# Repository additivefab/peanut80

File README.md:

# ZL80 R5.2｜80 mm 连续工业底片扫描仪

**当前设计基线更新于 2026-11-17，阶段为工程评审。** 从 [R5.2 融合设计基线](docs/ZL80_R52_融合评估与设计基线.md) 第 8 节进入，或打开 [离线目录](index.html)。

- [G4 板卡与装配](ZL80_R52_G4_20261116/START_HERE.html) 提供 B06/B07/B08 布线候选。B01 按 R5.2 双增益重版，B02–B05 待闭合。
- [G5 FPGA 与原始采集（Hello-FPGA 核心板修订）](ZL80_R52_G5_HF_20261117/START_HERE.html) 提供归一化采集核、第三路出口随动编码器和 ZL80RAW1 离线调试格式。Icarus 仿真通过；Vivado、B02 同 epoch 适配、时戳标定和 DMA 仍有待完成。
- [ADF50 V0.6](ZL80_ADF50_V06/README.md) 是现行馈片方案，单向走片、两处 R80 弯道，含已批准的 ECR-G3-01（出口随动编码器）、B05 第三路输入和线束。旧版 V01–V05 已于 2026-11-17 删除。

加工、投板和烧录状态为 BLOCKED。以下为 R5-PDR1 的原始交付说明，收光、板卡与馈片等变更以当前设计基线为准。

## R5-PDR1 原始交付

**交付日期：2026-11-14。阶段：光机电集成初步工程设计，不是加工/PCB投板放行。**

解压后打开`index.html`，无需联网浏览全部105张图纸。建议先看设计说明、D04板卡空间、D08积分筒剖面、D10 PMT接口、D13传感器、D17线束和E01–E08各板布局。

## 固定架构

80 mm有效幅宽；100 mm横扫预留；实体顶部狭缝104×1.2 mm。激光→准直/ND/参考取光→反射式旋转多面棱镜→f-theta→连续运动胶片→横置积分筒→径向侧窗→PMMA导光件→单PMT→模拟前端→DC耦合ADC→FPGA。圆筒轴X，片进给Y，Z向上，两端封闭。

首版模拟前端按新PPT采用线性TIA。原机LOG作为互斥的替换卡路线保留，不能把两者并接PMT。未设计普通相机、整线照明加单PMT或振镜替代路线。

## 本版关键改进

- 不只画板框：8块定制PCB草稿＋SP2托板定义了坐标、孔位、层数目标、上下器件高度、维护方向；84个关键器件或功能空间区域参与布置。
- PMT候选为H10720-20针脚式模块；8×10 mm入口导光件在输出端收至5.2 mm方形，针对φ8 mm有效光阴极重新起算。几何可容纳不代表导光效率已验证。
- PMT插座和短输入前端靠近布置；模拟舱、采集舱、驱动和开关电源分区；SP2接口按V1.3B并明确1.8/3.3/5V边界。
- 四辊连续走片，牵引与计量独立；SOS/EOS、参考PD、入出片、温度、开盖/失扫、可选馈片异常均在表格/图中定义位置及接口。
- 纳入插拔、线束、维护空间；关键器件突出空间与刚性核心复核；不把裸板能放入当成已完成整机装联。

## 文件目录

| 目录 | 内容 |
|---|---|
| docs | 25页设计说明PDF/DOCX及Markdown |
| drawings | 105页完整图册；32页系统+PCB；73页零件名义几何；逐张SVG/PNG |
| cad | 81个STEP、12个DXF、可编辑CadQuery脚本、装配坐标及空间限界 |
| electronics | 8个未布线KiCad PCB草稿、16张针脚/网名审查图、关键布局、接口/线束 |
| engineering | 13工作表Excel、预算JSON、机械/电子BOM、选型证据、14项冻结门槛 |
| firmware / software | 时序/编码器参考RTL与XDC、Python参考数据处理；不是可直接运行整机软件 |
| references | 原始资料、PPT逐页文本、照片、厂家来源登记 |
| tests | 实际执行的几何、空间、公式、文件版面和35项Python测试记录 |
| tools | 辅助生成/检查源代码与依赖说明 |

## 本次已执行检查

73个名义CAD形体有效，核心刚性件未发现体积重叠；关键器件空间盒与核心件复核无未解决碰撞（PMT插针/插座等预期接合单独标记）。35项计算和参考数据链测试通过。PDF最终渲染和Excel公式已检查。

这些检查**不代表**真实光学、PMT线性、高OD信噪比、胶片无划伤、EMC/安全或寿命已经合格。没有运行KiCad原生ERC/DRC，也没有完成RTL综合与时序验证。

## 明确未关闭的设计事项

关键光学器件需联合RFQ并锁定真实处方、工作距离和全视场光斑；SP2的110×60×25 mm仅保守安装限界，孔距/接口位置需实测；编码器量化步距不代表真实走片精度。B03/B04/B05等FUNCTION_ONLY区域需完成器件级电路、外围、焊盘、保护和完整PCB布线；全紧固、公差链、线束弯曲、装配工艺仍需深化。**本包不提供Gerber，不应按此直接下单生产。**

本版主机安装包络320×300×300 mm，不含外置卷架/馈片器。基座与铝外罩名义质量已约4.33 kg，整机试制预算6–8 kg待称重；**早期≤3.5 kg便携目标尚未实现**。优先验证核心链路后再进行减重和小型化，而非用缩小的占位盒宣称目标已达成。

## 数据/版本

文件校验见`manifest_sha256.json`。`release_status.json`为机器可读交付状态。所有性能数值注明来源或“设计假设/目标”，样机数据尚未提供。Raw Master和Calibrated Master与显示/AI派生图分开保存。

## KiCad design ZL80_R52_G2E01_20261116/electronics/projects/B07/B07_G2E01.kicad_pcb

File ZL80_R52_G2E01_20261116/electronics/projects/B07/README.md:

# B07 G2-E01

打开 B07_G2E01.kicad_pro。原理图是元件级候选；PCB有板框/孔/封装/网络及初排，尚无布线。

- 3V3 push-pull SYNC; J1 pin1 remains +5V input, NOT 3V3 input.
- S5971: 1=K, 3=A, 2=CASE. Case tied GND. Reverse bias ~1V; no 100MHz claim.
- R3 adds positive feedback; TLV3501 SHDN tied low. Full light pulse is outside image ROI.
- Threshold/optical amplitude not measured. 5um timing budget is NOT yet passed.
- C6 at U1 and C7 at U2. Keep PD_SUM/feedback short; do not connect a long test lead to PD_SUM.
- Use short grounded harness for PoC. Long cable requires a differential link change request.

状态：NOT_RELEASED。仿真为有限模型证据；没有台架结果。

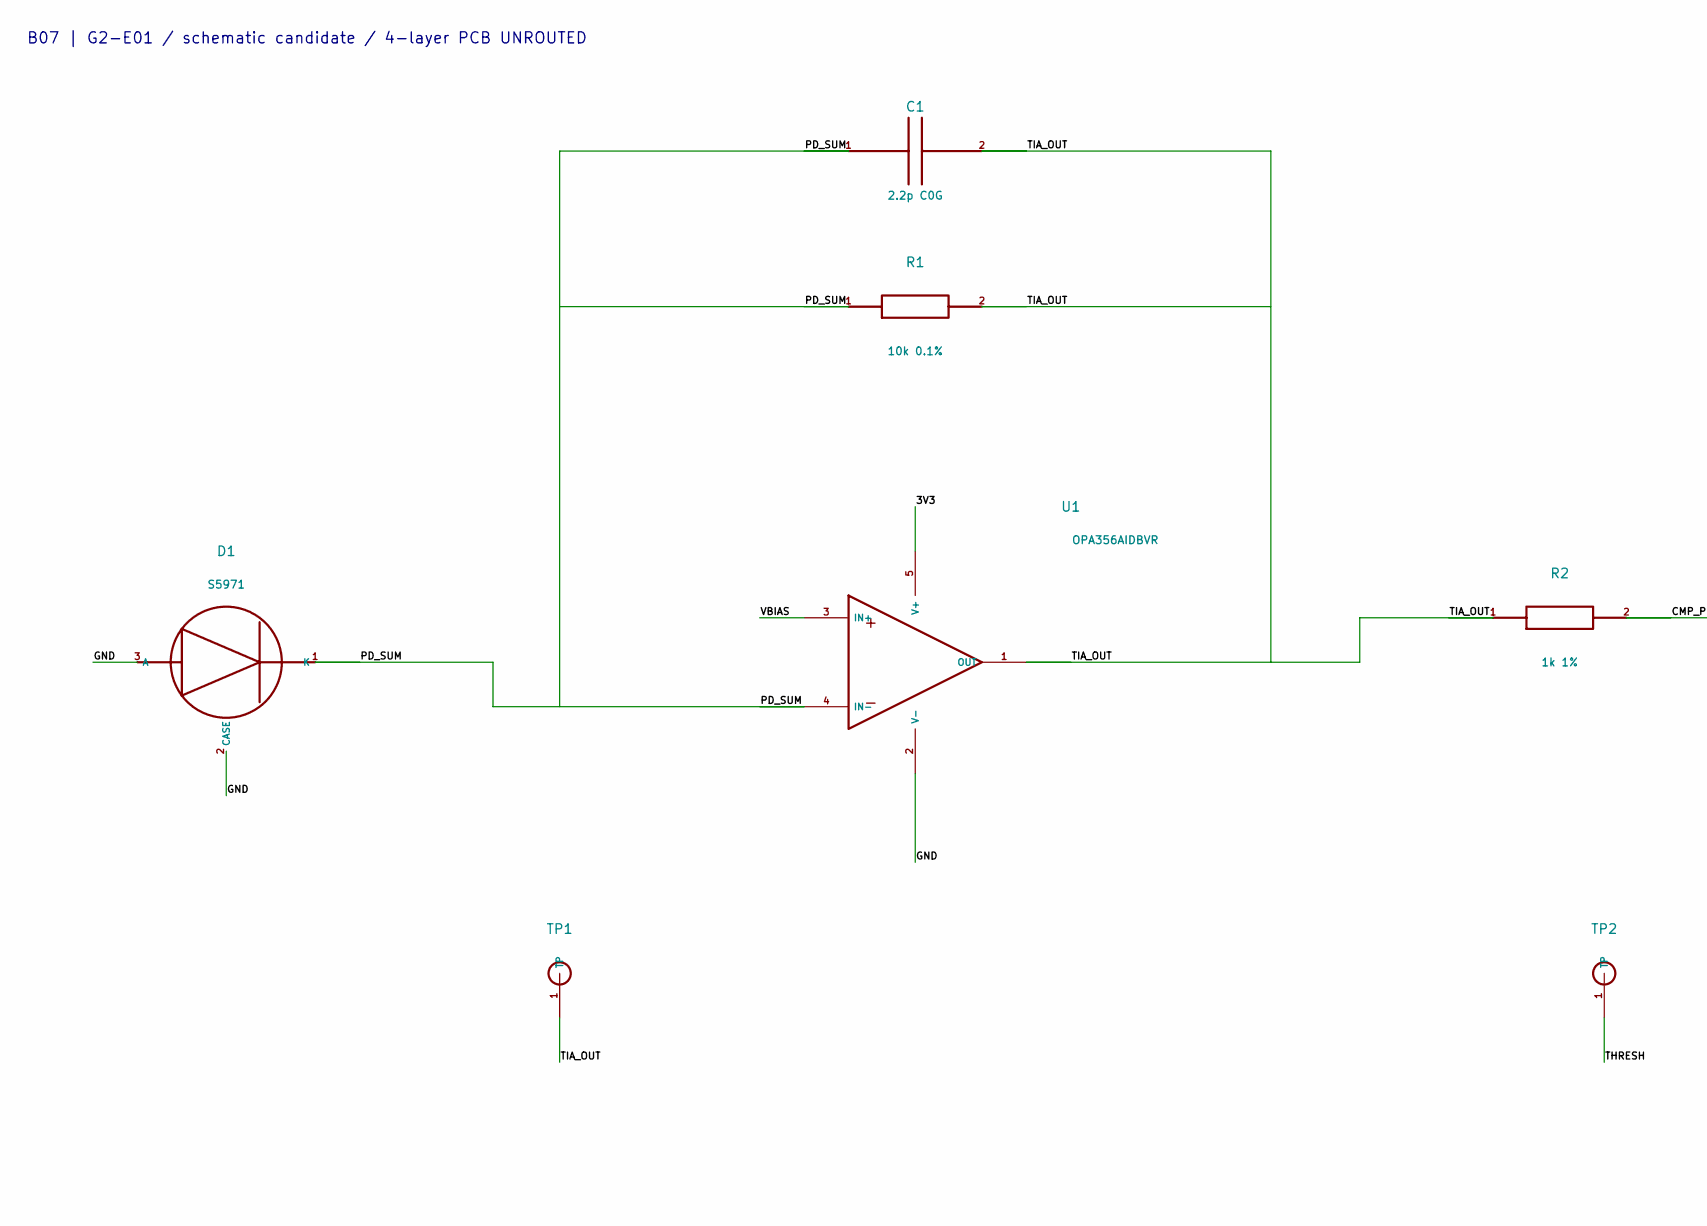
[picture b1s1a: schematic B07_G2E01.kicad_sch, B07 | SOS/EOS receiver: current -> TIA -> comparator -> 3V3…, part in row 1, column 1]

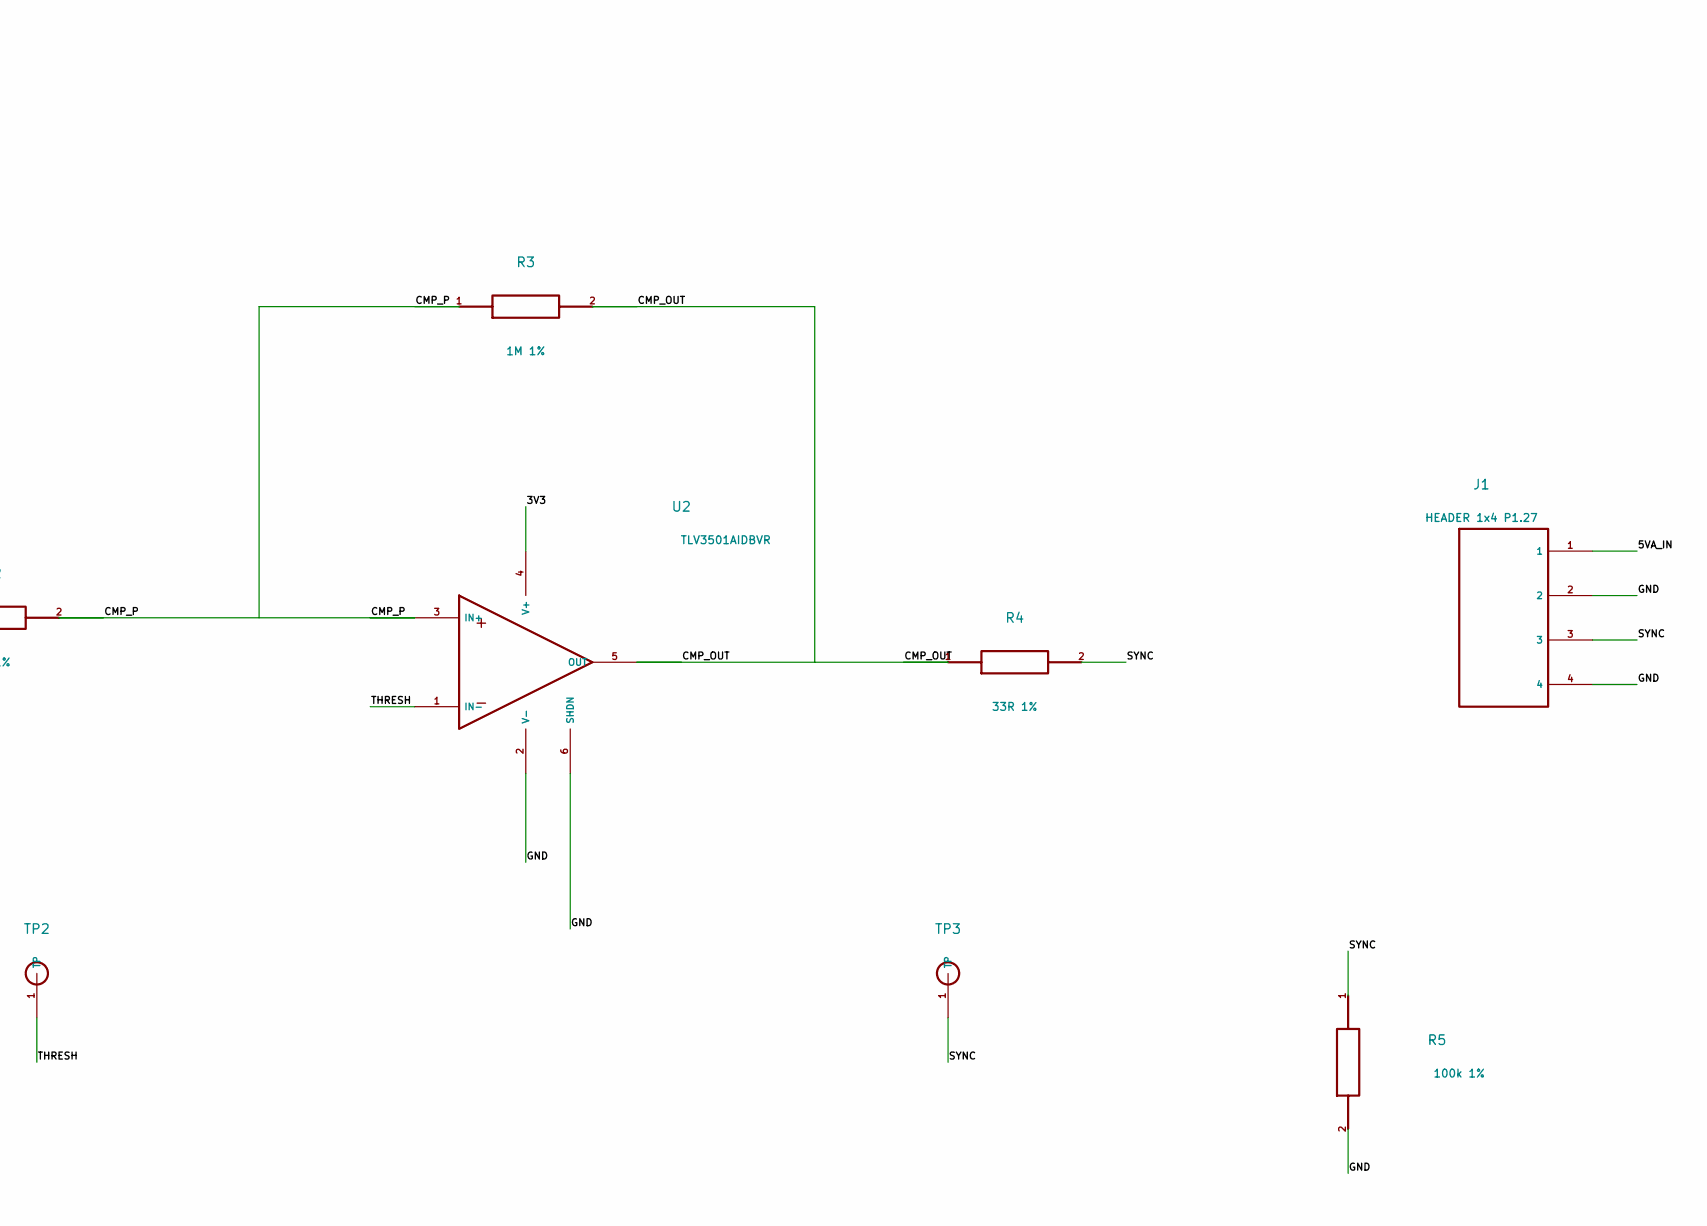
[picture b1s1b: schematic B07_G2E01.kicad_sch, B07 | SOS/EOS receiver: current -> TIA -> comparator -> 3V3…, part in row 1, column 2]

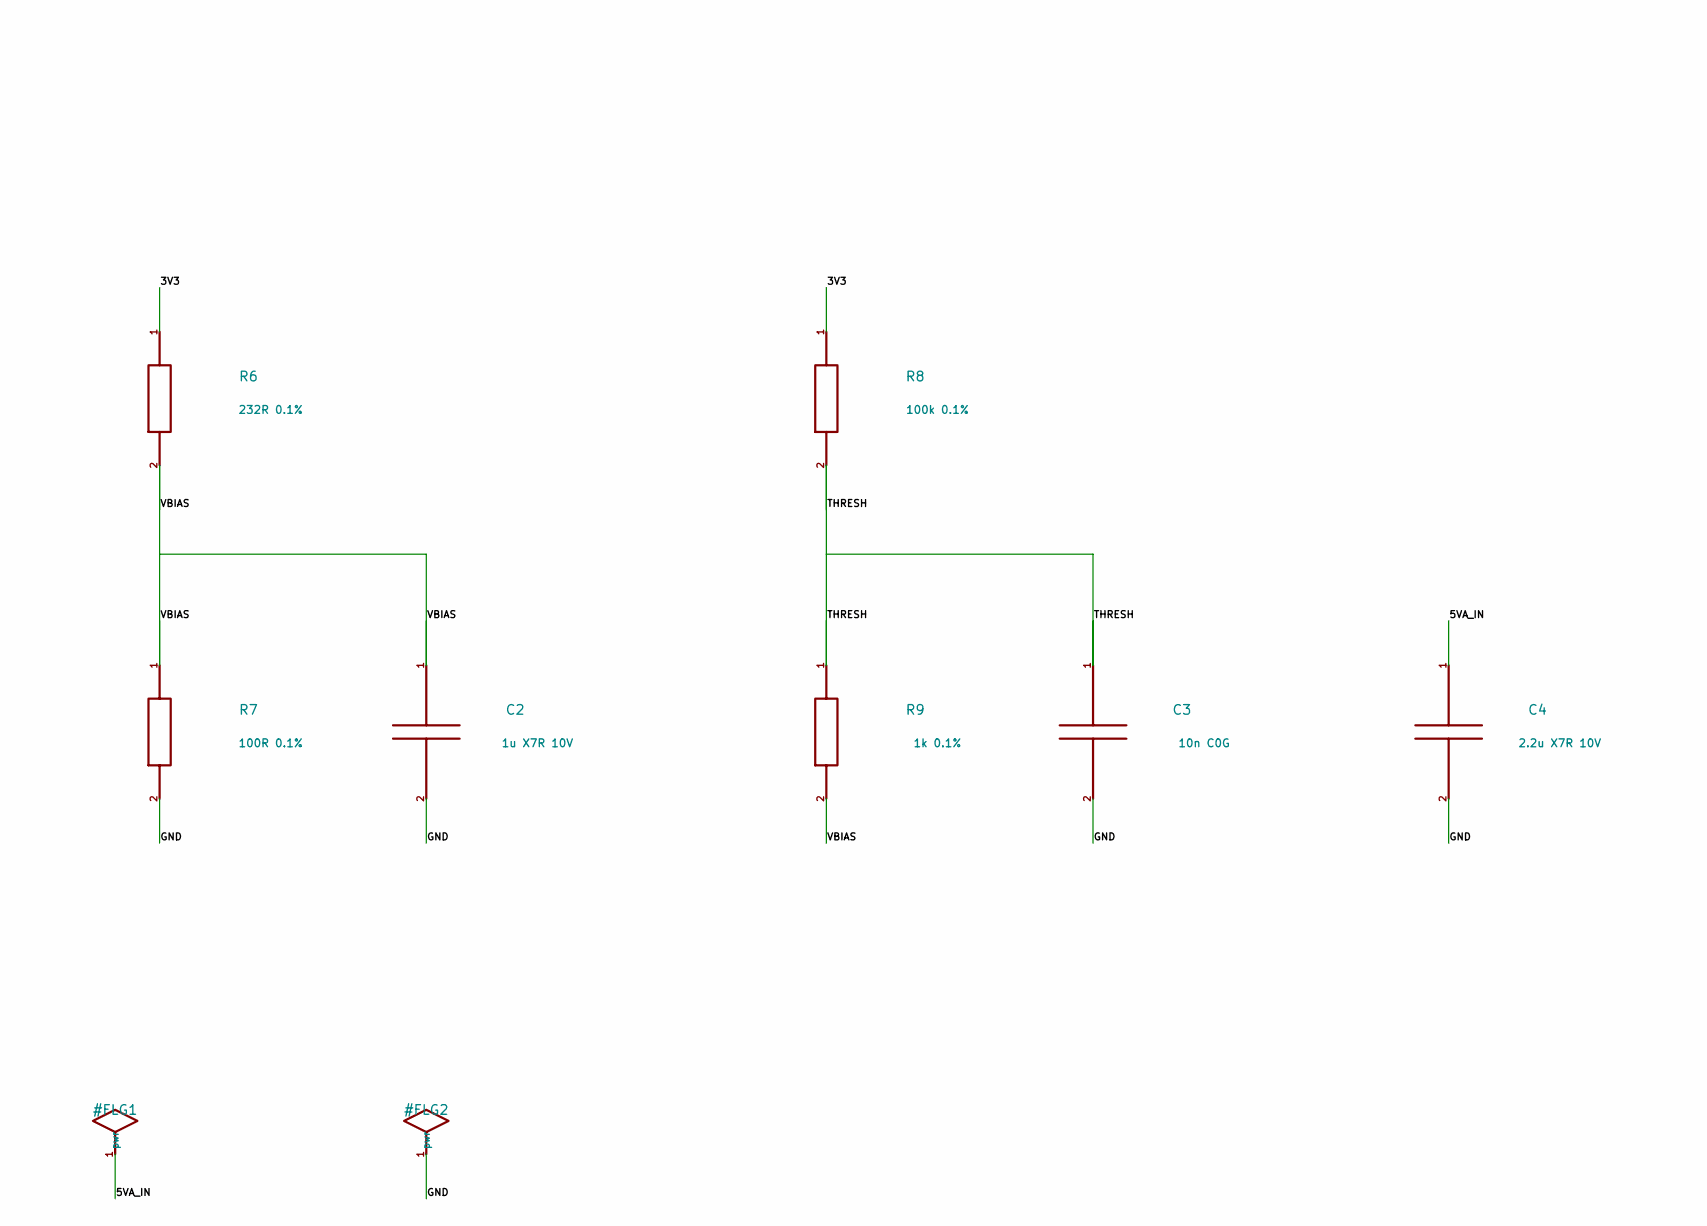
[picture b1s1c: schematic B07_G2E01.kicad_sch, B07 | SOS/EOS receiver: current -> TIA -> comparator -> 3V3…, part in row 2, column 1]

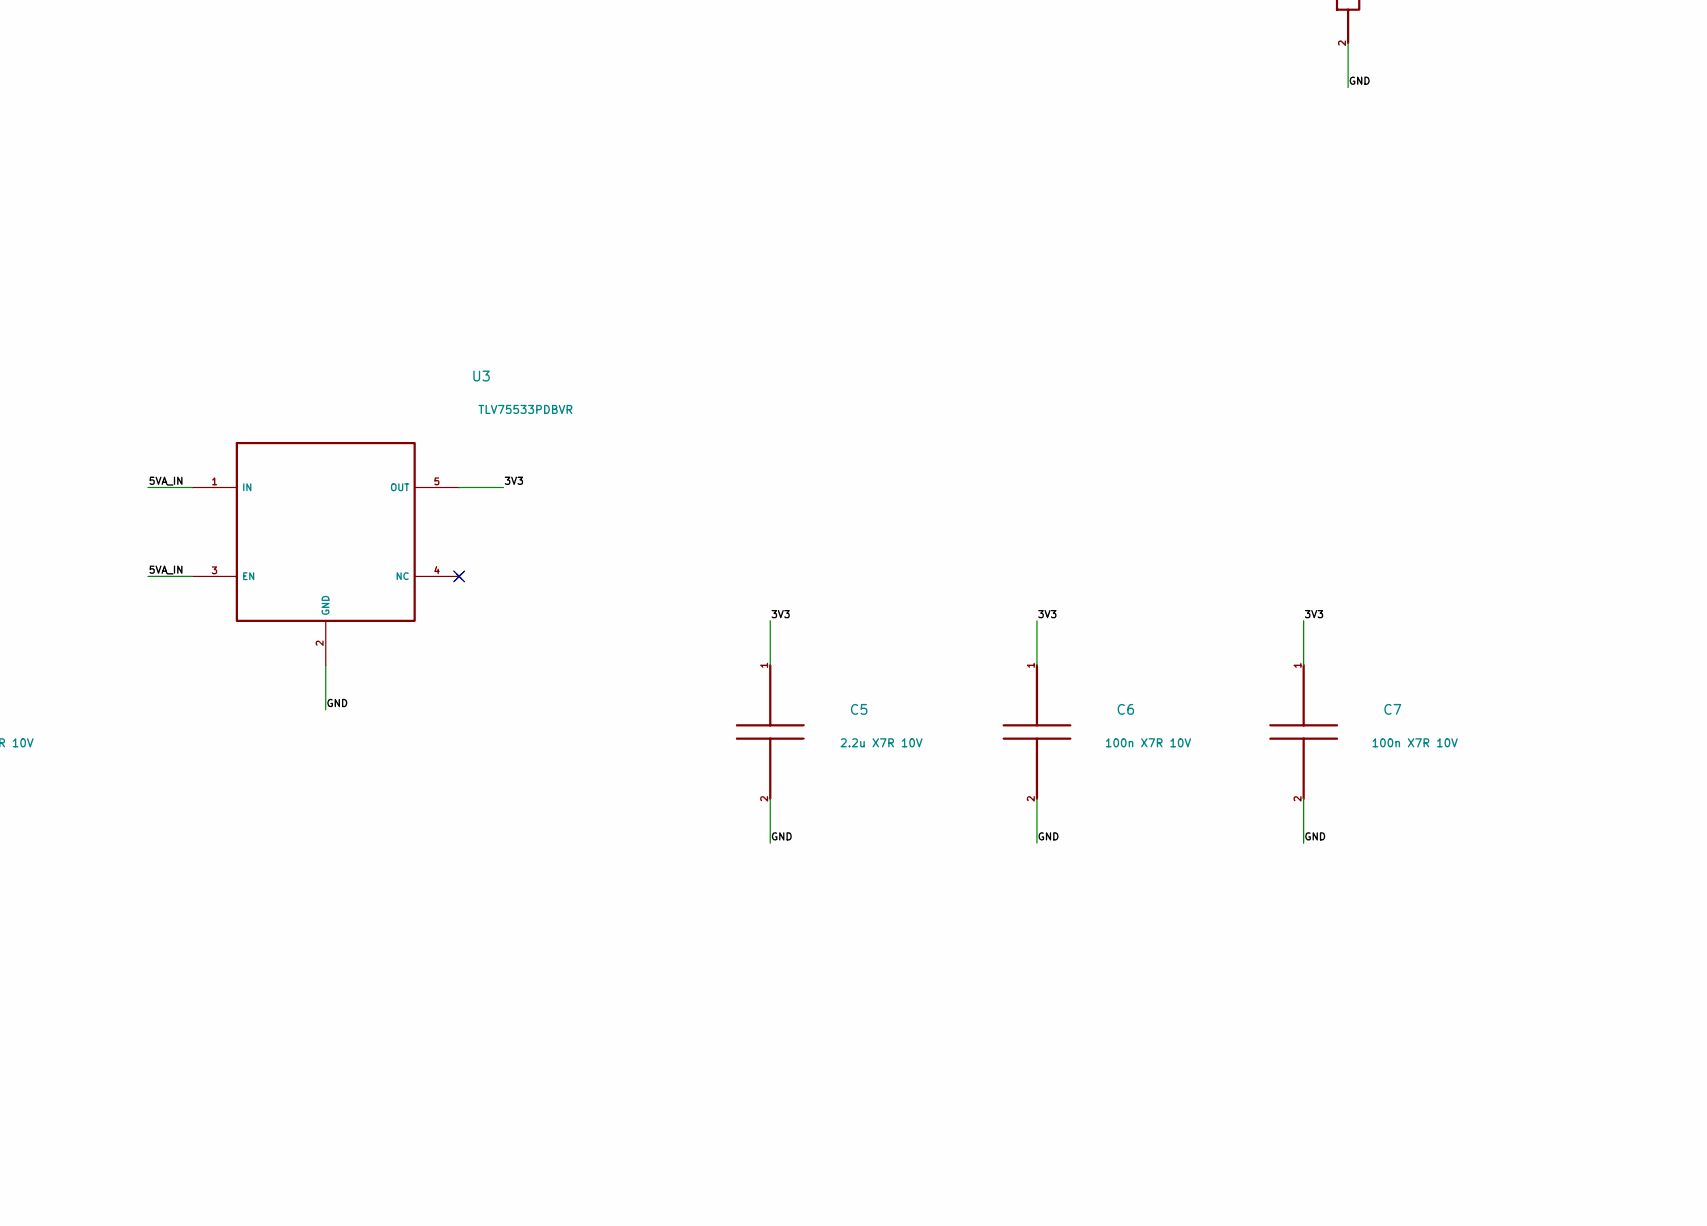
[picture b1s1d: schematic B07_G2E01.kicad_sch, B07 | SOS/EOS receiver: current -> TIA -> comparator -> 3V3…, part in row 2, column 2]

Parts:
C1: 2.2p C0G; 0603
C2: 1u X7R 10V; 0603
C3: 10n C0G; 0603
C4, C5: 2.2u X7R 10V; 0603
C6, C7: 100n X7R 10V; 0603
D1: S5971; S5971_TO18_TOP; ManufacturerPartNumber S5971
J1: HEADER 1x4 P1.27; HDR4
R1: 10k 0.1%; 0603
R2: 1k 1%; 0603
R3: 1M 1%; 0603
R4: 33R 1%; 0603
R5: 100k 1%; 0603
R6: 232R 0.1%; 0603
R7: 100R 0.1%; 0603
R8: 100k 0.1%; 0603
R9: 1k 0.1%; 0603
TP1: TIA_OUT; TP1
TP2: THRESH; TP1
TP3: SYNC; TP1
U1: OPA356AIDBVR; SOT23_5; ManufacturerPartNumber OPA356AIDBVR
U2: TLV3501AIDBVR; SOT23_6; ManufacturerPartNumber TLV3501AIDBVR
U3: TLV75533PDBVR; SOT23_5; ManufacturerPartNumber TLV75533PDBVR

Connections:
3V3: C5.1, C6.1, C7.1, R6.1, R8.1, U1.5 (V+), U2.4 (V+), U3.5 (OUT)
5VA_IN: C4.1, J1.1, U3.1 (IN), U3.3 (EN)
CMP_OUT: R3.2, R4.1, U2.5 (OUT)
CMP_P: R2.2, R3.1, U2.3 (IN+)
GND: C2.2, C3.2, C4.2, C5.2, C6.2, C7.2, D1.2 (CASE), D1.3 (A), J1.2, J1.4, R5.2, R7.2, U1.2 (V-), U2.2 (V-), U2.6 (SHDN), U3.2 (GND)
PD_SUM: C1.1, D1.1 (K), R1.1, U1.4 (IN-)
SYNC: J1.3, R4.2, R5.1, TP3.1
THRESH: C3.1, R8.2, R9.1, TP2.1, U2.1 (IN-)
TIA_OUT: C1.2, R1.2, R2.1, TP1.1, U1.1 (OUT)
VBIAS: C2.1, R6.2, R7.1, R9.2, U1.3 (IN+)

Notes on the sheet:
B07 | G2-E01 / schematic candidate / 4-layer PCB UNROUTED

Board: 4 copper layers, 28 parts (0 on the bottom side), 10 nets, no tracks yet.

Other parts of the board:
H1, H2, H3, H4: NPTH

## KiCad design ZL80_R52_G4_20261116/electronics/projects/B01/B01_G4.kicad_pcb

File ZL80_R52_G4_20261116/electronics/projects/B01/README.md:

# B01 G4

B01_G4.kicad_pro 为入口。原理图拓扑继承G2；PCB包含实际铜线和过孔。B01仅输入/TIA关键网布线，其余故意保持未连。所有铺铜必须在KiCad重新填充，运行ERC/DRC和原理图一致性检查。禁止直接下单。

G4所有小板无台架实测，无原生KiCad验证。0402焊接/清洗、接插件对接、PD方向和插针需人工复核。

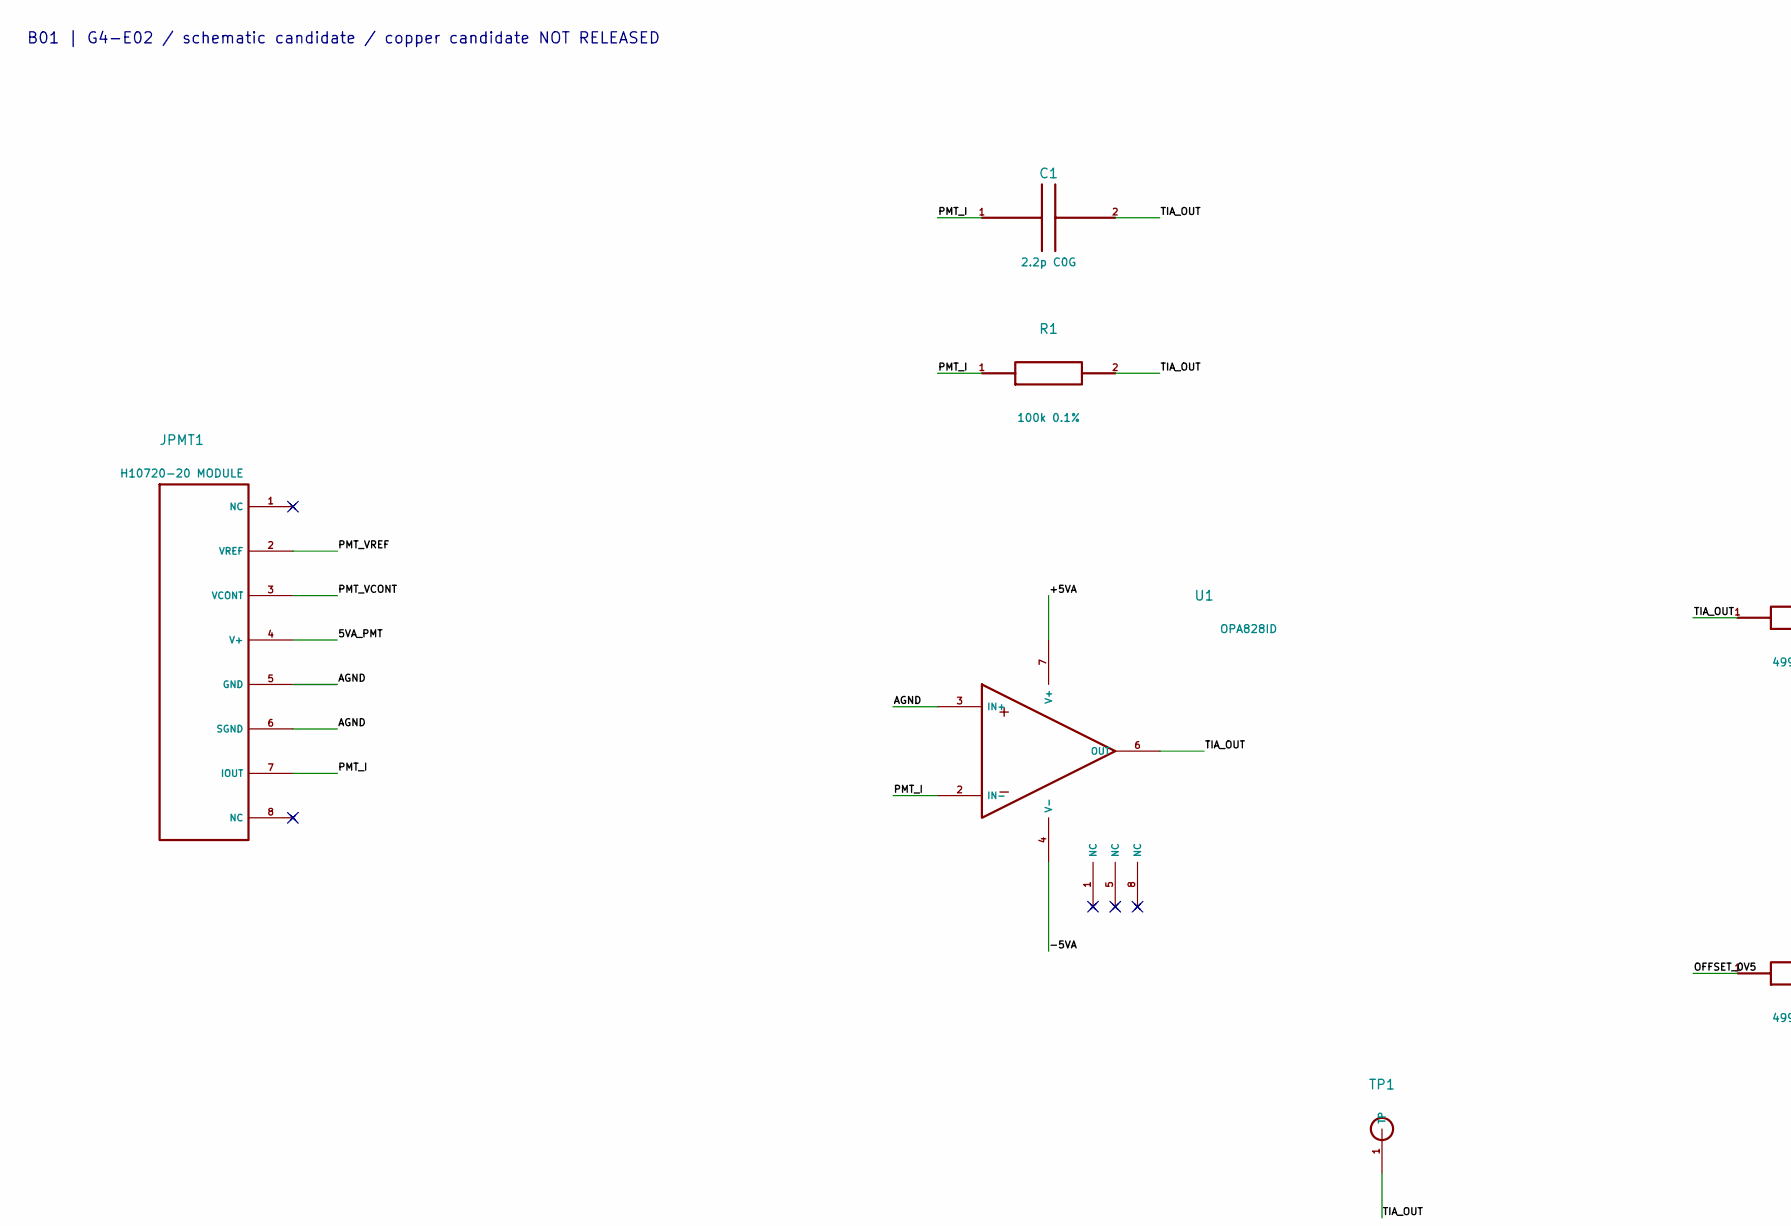
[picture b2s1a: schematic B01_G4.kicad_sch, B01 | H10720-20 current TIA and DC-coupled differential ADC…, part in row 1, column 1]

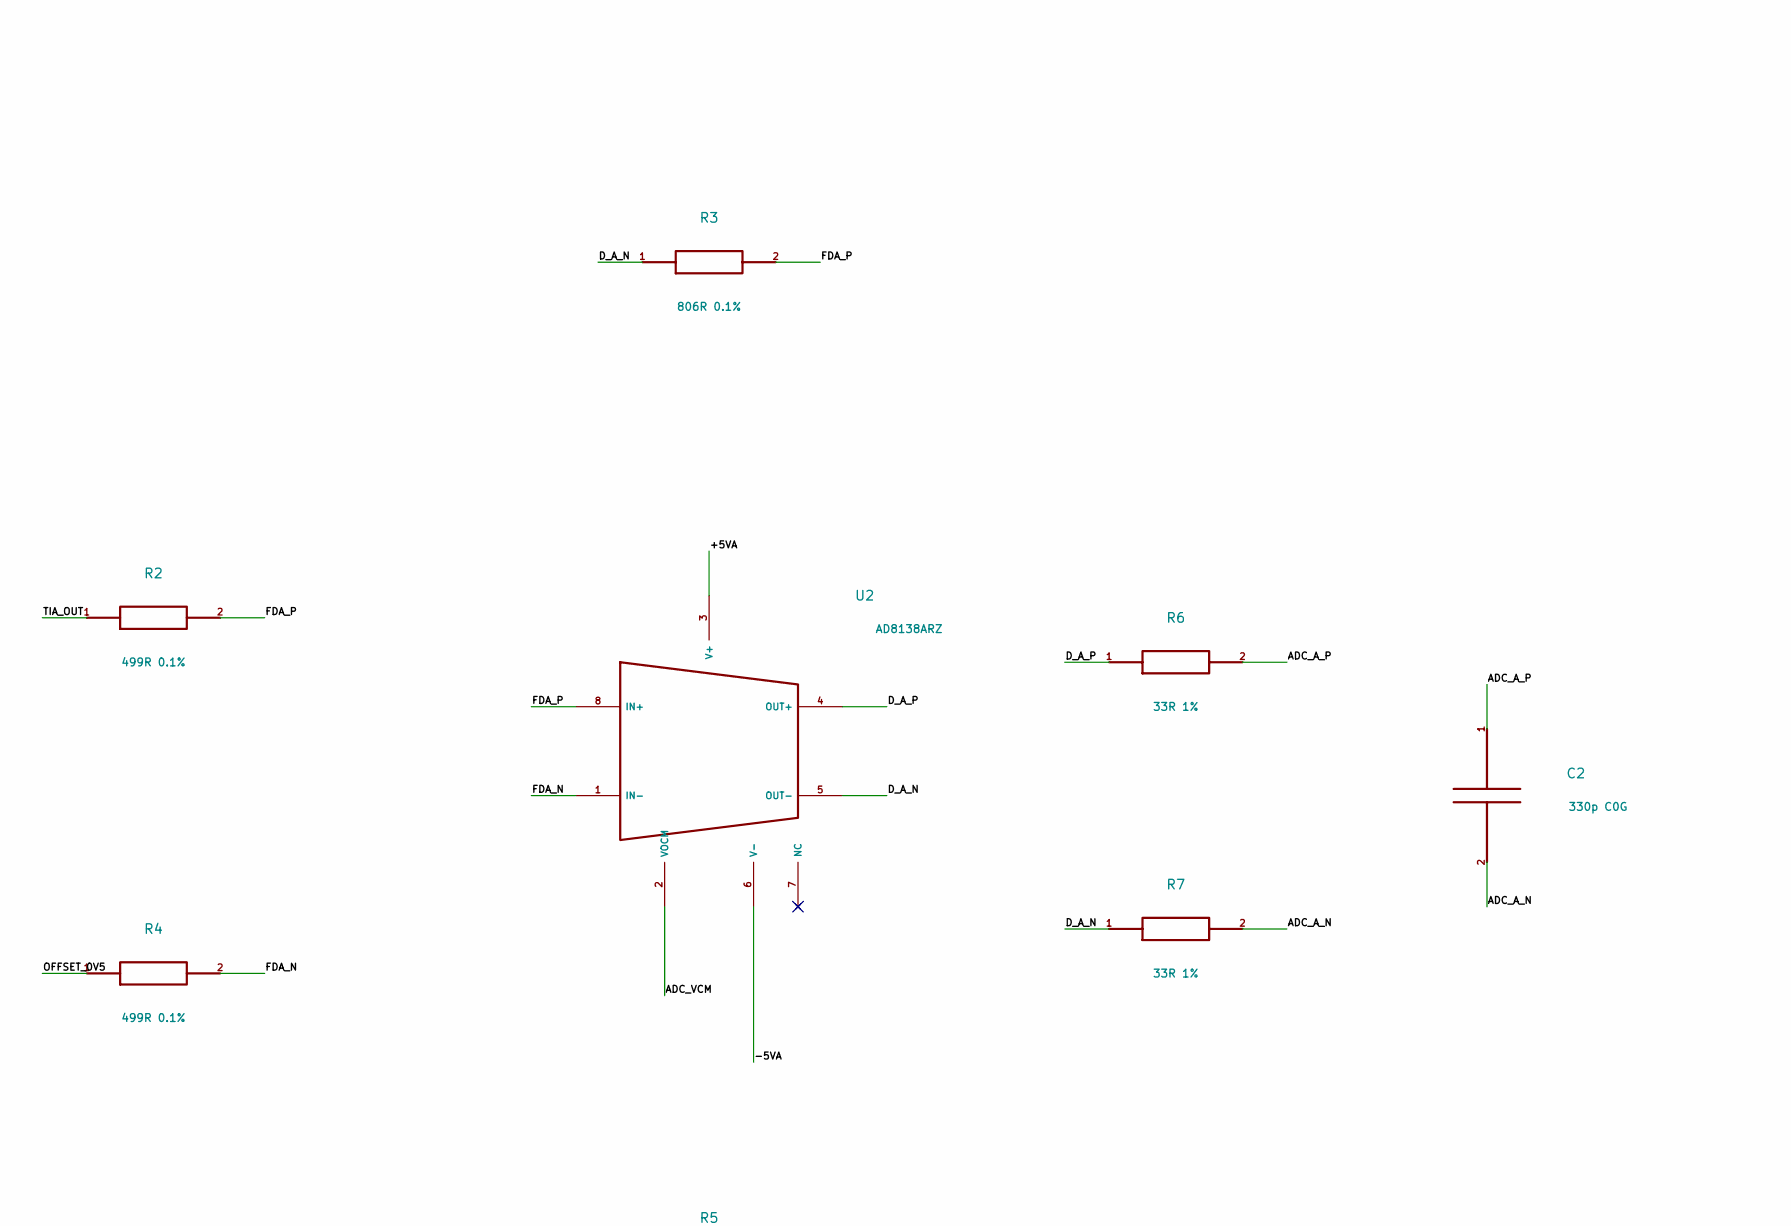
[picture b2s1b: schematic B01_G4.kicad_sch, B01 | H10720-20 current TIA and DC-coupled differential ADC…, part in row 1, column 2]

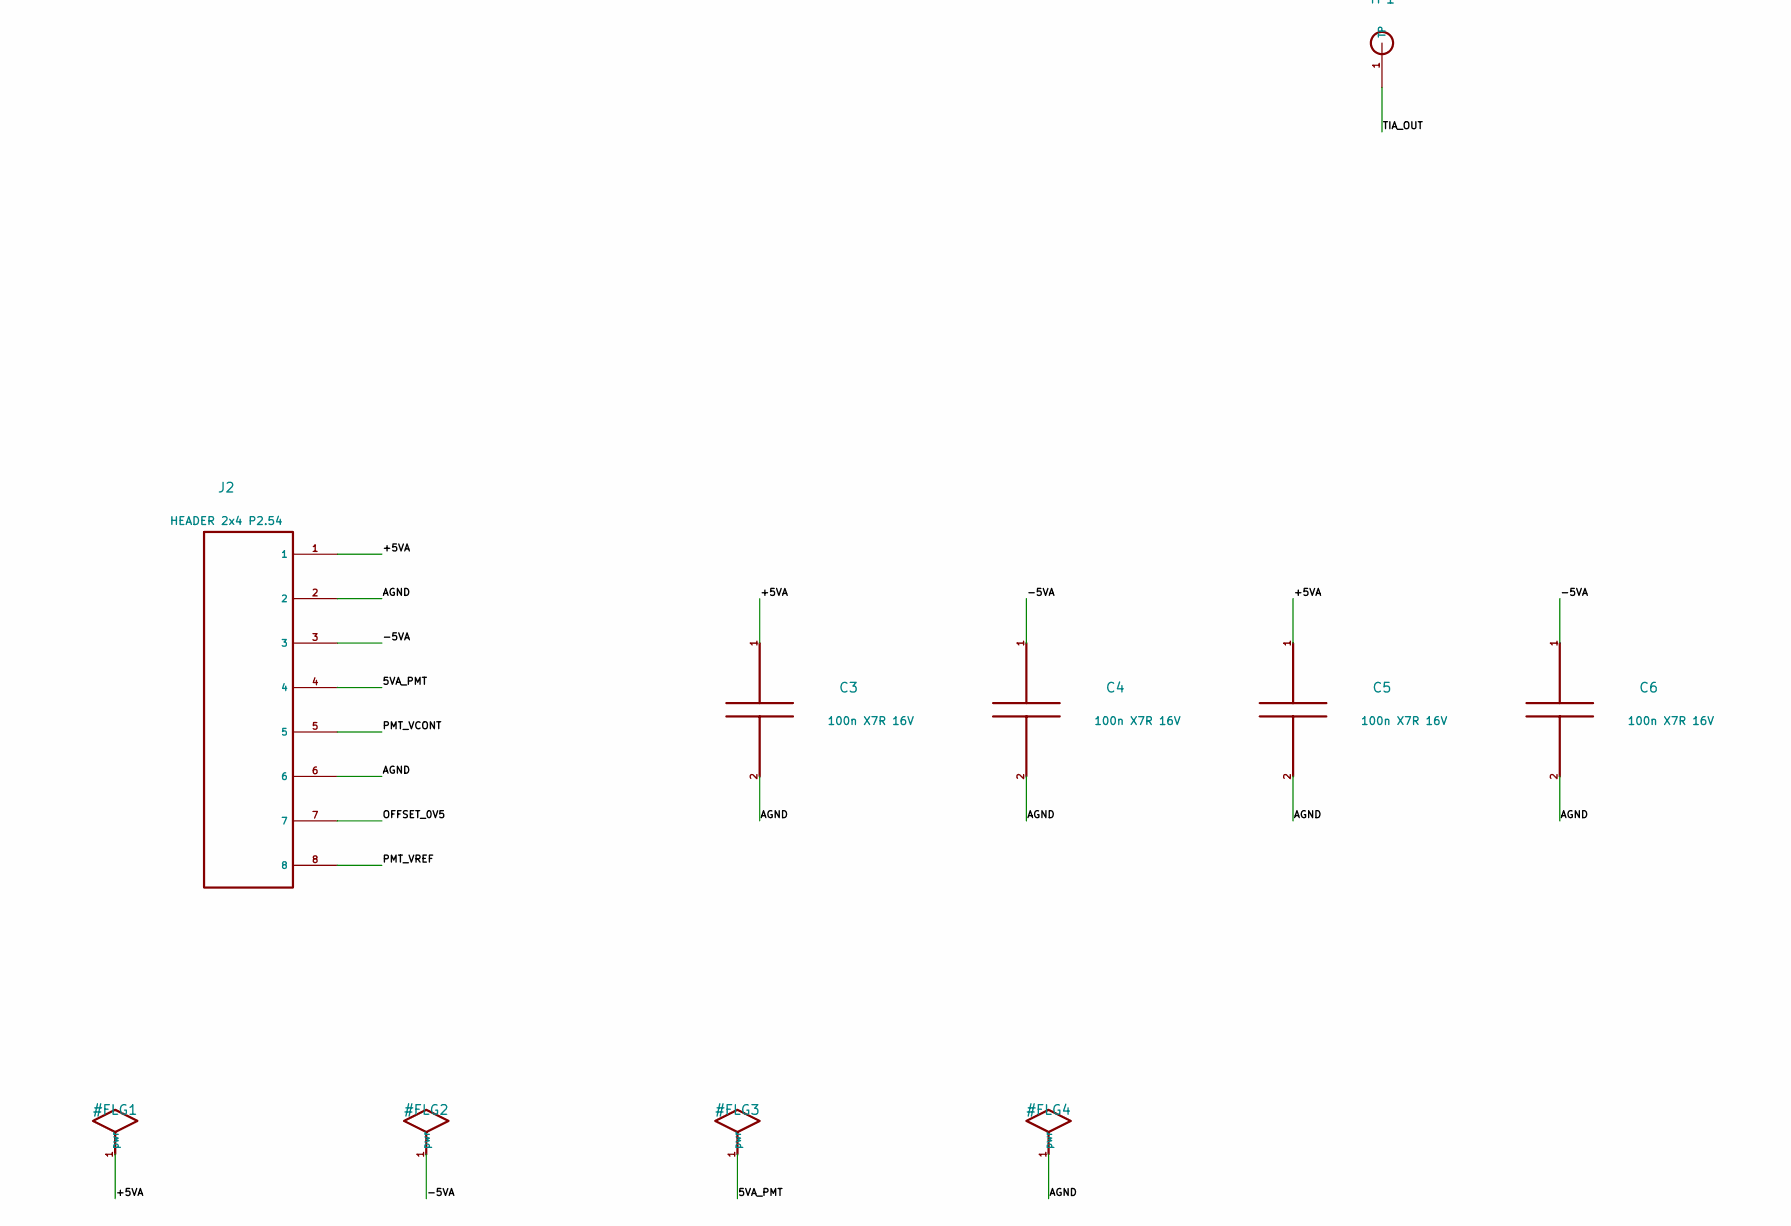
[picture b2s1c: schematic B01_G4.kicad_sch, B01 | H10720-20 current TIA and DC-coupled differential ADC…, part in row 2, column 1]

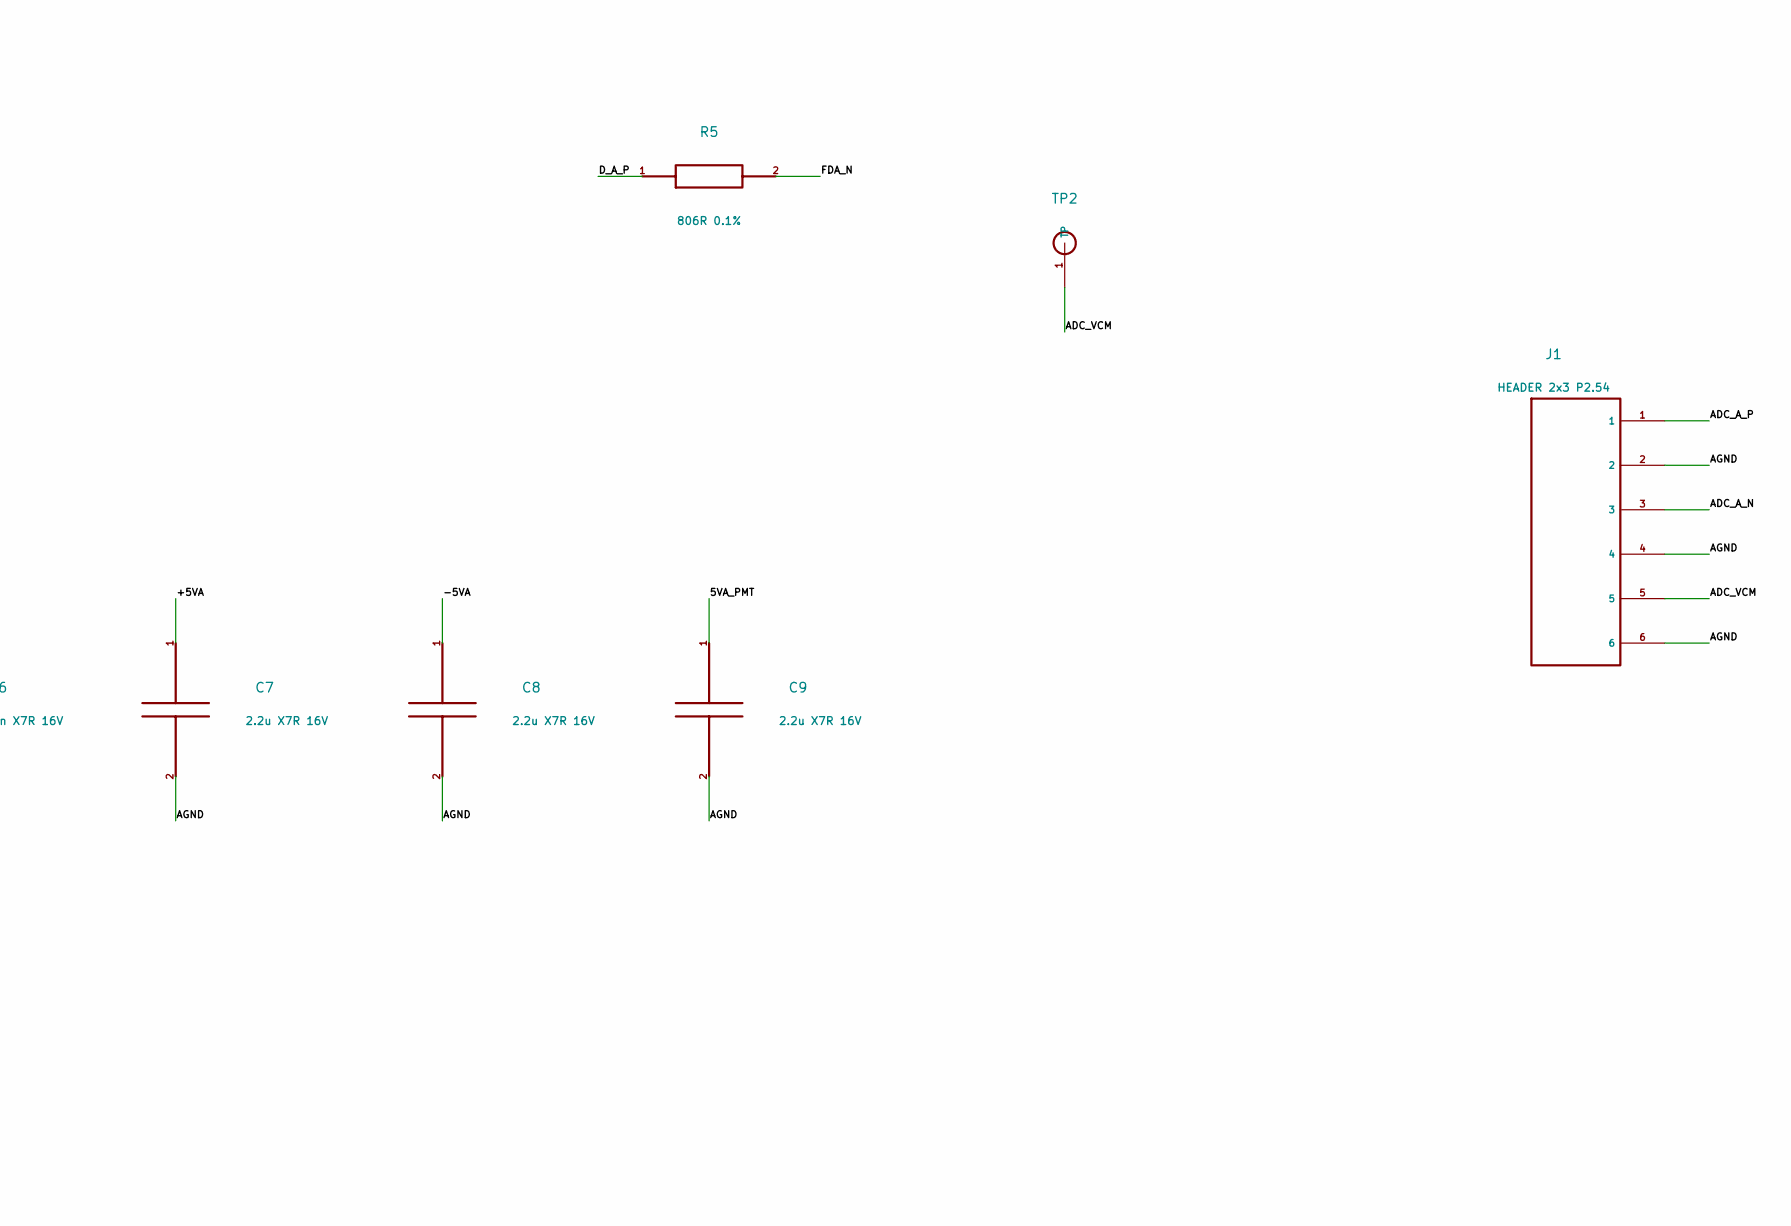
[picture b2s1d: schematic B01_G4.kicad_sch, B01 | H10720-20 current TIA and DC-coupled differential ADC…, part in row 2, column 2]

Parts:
C1: 2.2p C0G; 0402
C2: 330p C0G; 0402
C3, C4, C5, C6: 100n X7R 16V; 0402
C7, C8, C9: 2.2u X7R 16V; 0603
J1: HEADER 2x3 P2.54; HDR6
J2: HEADER 2x4 P2.54; HDR8
JPMT1: H10720-20 MODULE; H10720_SOCKET_DRAFT; ManufacturerPartNumber H10720-20
R1: 100k 0.1%; 0402
R2, R4: 499R 0.1%; 0402
R3, R5: 806R 0.1%; 0402
R6, R7: 33R 1%; 0402
TP1: TIA_OUT; TP1
TP2: ADC_VCM; TP1
U1: OPA828ID; SOIC8; ManufacturerPartNumber OPA828ID
U2: AD8138ARZ; SOIC8; ManufacturerPartNumber AD8138ARZ

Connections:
5VA_PMT: C9.1, J2.4, JPMT1.4 (V+)
+5VA: C3.1, C5.1, C7.1, J2.1, U1.7 (V+), U2.3 (V+)
-5VA: C4.1, C6.1, C8.1, J2.3, U1.4 (V-), U2.6 (V-)
ADC_A_N: C2.2, J1.3, R7.2
ADC_A_P: C2.1, J1.1, R6.2
ADC_VCM: J1.5, TP2.1, U2.2 (VOCM)
AGND: C3.2, C4.2, C5.2, C6.2, C7.2, C8.2, C9.2, J1.2, J1.4, J1.6, J2.2, J2.6, JPMT1.5 (GND), JPMT1.6 (SGND), U1.3 (IN+)
D_A_N: R3.1, R7.1, U2.5 (OUT-)
D_A_P: R5.1, R6.1, U2.4 (OUT+)
FDA_N: R4.2, R5.2, U2.1 (IN-)
FDA_P: R2.2, R3.2, U2.8 (IN+)
OFFSET_0V5: J2.7, R4.1
PMT_I: C1.1, JPMT1.7 (IOUT), R1.1, U1.2 (IN-)
PMT_VCONT: J2.5, JPMT1.3 (VCONT)
PMT_VREF: J2.8, JPMT1.2 (VREF)
TIA_OUT: C1.2, R1.2, R2.1, TP1.1, U1.6 (OUT)

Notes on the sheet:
B01 | G4-E02 / schematic candidate / copper candidate NOT RELEASED

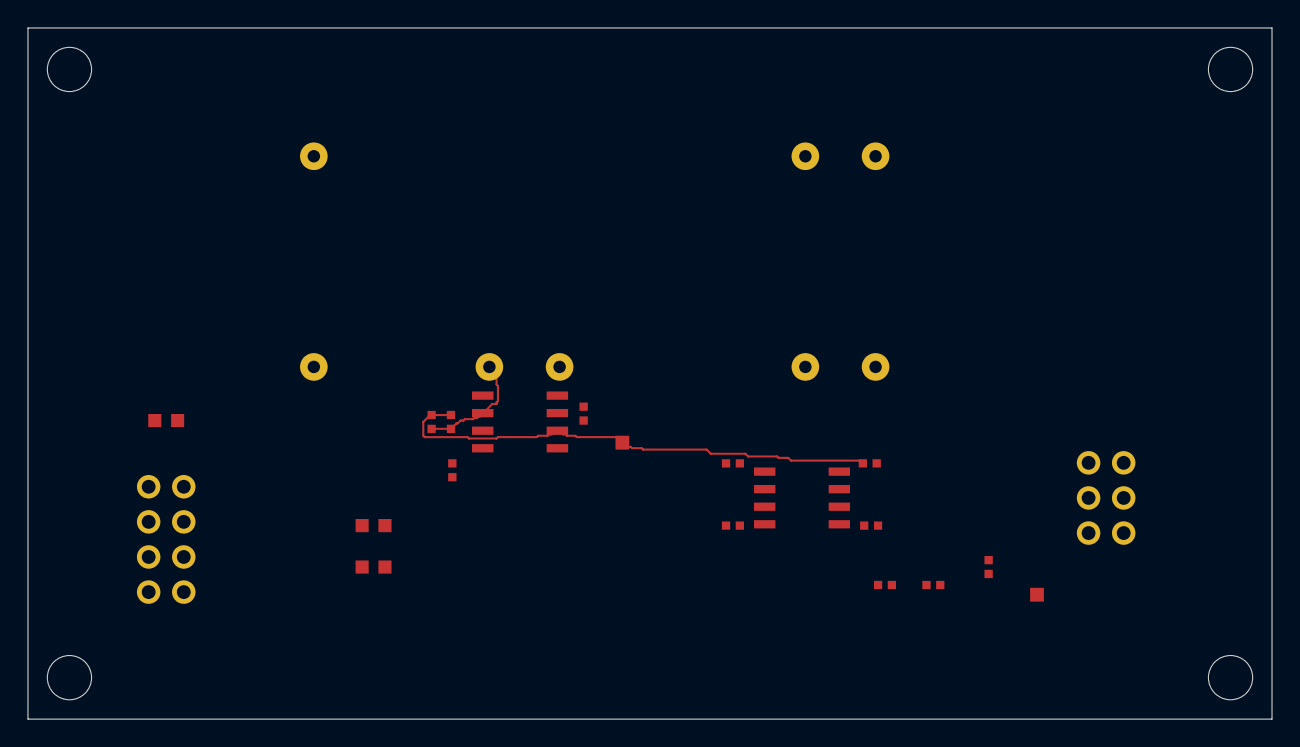
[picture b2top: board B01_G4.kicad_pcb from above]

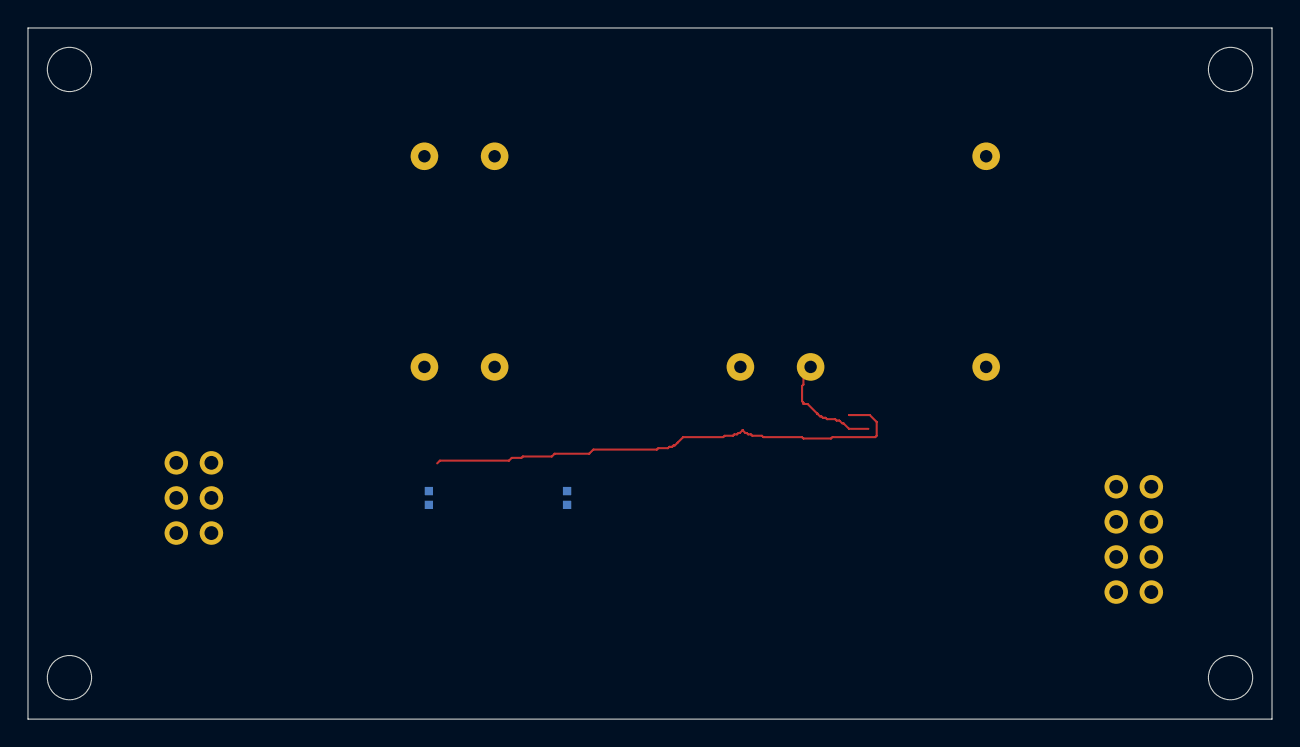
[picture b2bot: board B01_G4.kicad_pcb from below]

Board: 4 copper layers, 90.0 x 50.0 mm, 27 parts (2 on the bottom side), 16 nets.

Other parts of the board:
H1, H2, H3, H4: NPTH
